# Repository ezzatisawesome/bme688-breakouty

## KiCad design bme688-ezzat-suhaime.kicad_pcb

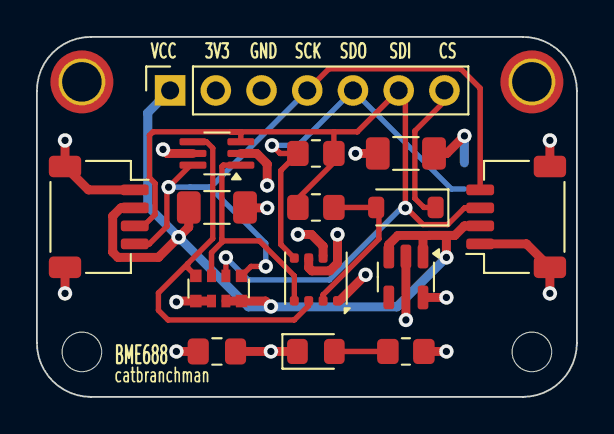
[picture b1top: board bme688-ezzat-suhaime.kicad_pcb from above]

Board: 4 copper layers, 30.0 x 20.0 mm, 20 parts (1 on the bottom side), 11 nets.

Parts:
C1, C2: 10uF; C_1206_3216Metric_Pad1.33x1.80mm_HandSolder
C3: 0.1uF; C_0805_2012Metric_Pad1.18x1.45mm_HandSolder
D1: 1N4148W; D_SOD-123
D2: LED; LED_0805_2012Metric_Pad1.15x1.40mm_HandSolder
H1, H2: MountingHole_Pad; MountingHole_2.2mm_M2_ISO7380_Pad_TopBottom
H3, H4: MountingHole; MountingHole_2.2mm_M2_ISO7380
J1: Conn_01x07; PinSocket_1x07_P2.54mm_Vertical
J2, J3: STEMMA_I2C_QT; JST_SH_SM04B-SRSS-TB_1x04-1MP_P1.00mm_Horizontal
JP1: SolderJumper_2_Open; SolderJumper-2_P1.3mm_Open_TrianglePad1.0x1.5mm
Q1: BSS138BKS,115; SOT-363_SC-70-6_Handsoldering
R1, R2, R3: 10kΩ; R_0805_2012Metric_Pad1.20x1.40mm_HandSolder
RN1: 10kΩ; R_Array_Convex_4x0612
U1: BME688; Bosch_LGA-8_3x3mm_P0.8mm_ClockwisePinNumbering
U2: XC6210B332MR-G; SOT-23-5

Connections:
+3.3V: C2.1, C3.1, J1.2, Q1.2 (G), Q1.5 (G), R3.1, RN1.5 (R4.2), RN1.6 (R3.2), U1.6 (VDDIO), U1.8 (VDD), U2.5 (OUT)
/CS: D1.1 (K), J1.7
/CS_3V: D1.2 (A), R1.2, U1.2 (CSB)
/SCK_3V: Q1.1 (S), RN1.3 (R3.1), U1.4 (SCK)
/SCK/SCL: J1.4, J2.4, J3.4, Q1.6 (D), RN1.1 (R1.1)
/SDI_3V: Q1.4 (S), RN1.4 (R4.1), U1.3 (SDI)
/SDI/SDA: J1.6, J2.3, J3.3, Q1.3 (D), R1.1, R2.1, RN1.2 (R2.1)
/SDO/ADR: J1.5, JP1.1 (A), R2.2, U1.5 (SDO)
GND: C1.2, C2.2, C3.2, D2.1 (K), J1.3, J2.1, J2.MP (Mounting_Pad), J3.1, J3.MP (Mounting_Pad), JP1.2 (B), U1.1 (GND), U1.7 (GND), U2.2 (GND)
unnamed: D2.2 (A), R3.2
VCC: C1.1, J1.1, J2.2, J3.2, RN1.7 (R2.2), RN1.8 (R1.2), U2.1 (IN), U2.3 (EN)

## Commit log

2024-10-21 Adding pcb stacking stripes
2024-10-21 Fixes per Steve & Brian
2024-10-27 Generate new drill and gerber files
2024-11-11 Adding ibom
